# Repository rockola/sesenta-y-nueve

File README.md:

# sesenta-y-nueve

Late 60s Boutique NPN Fuzz Face

* 0.1: initial version, unverified

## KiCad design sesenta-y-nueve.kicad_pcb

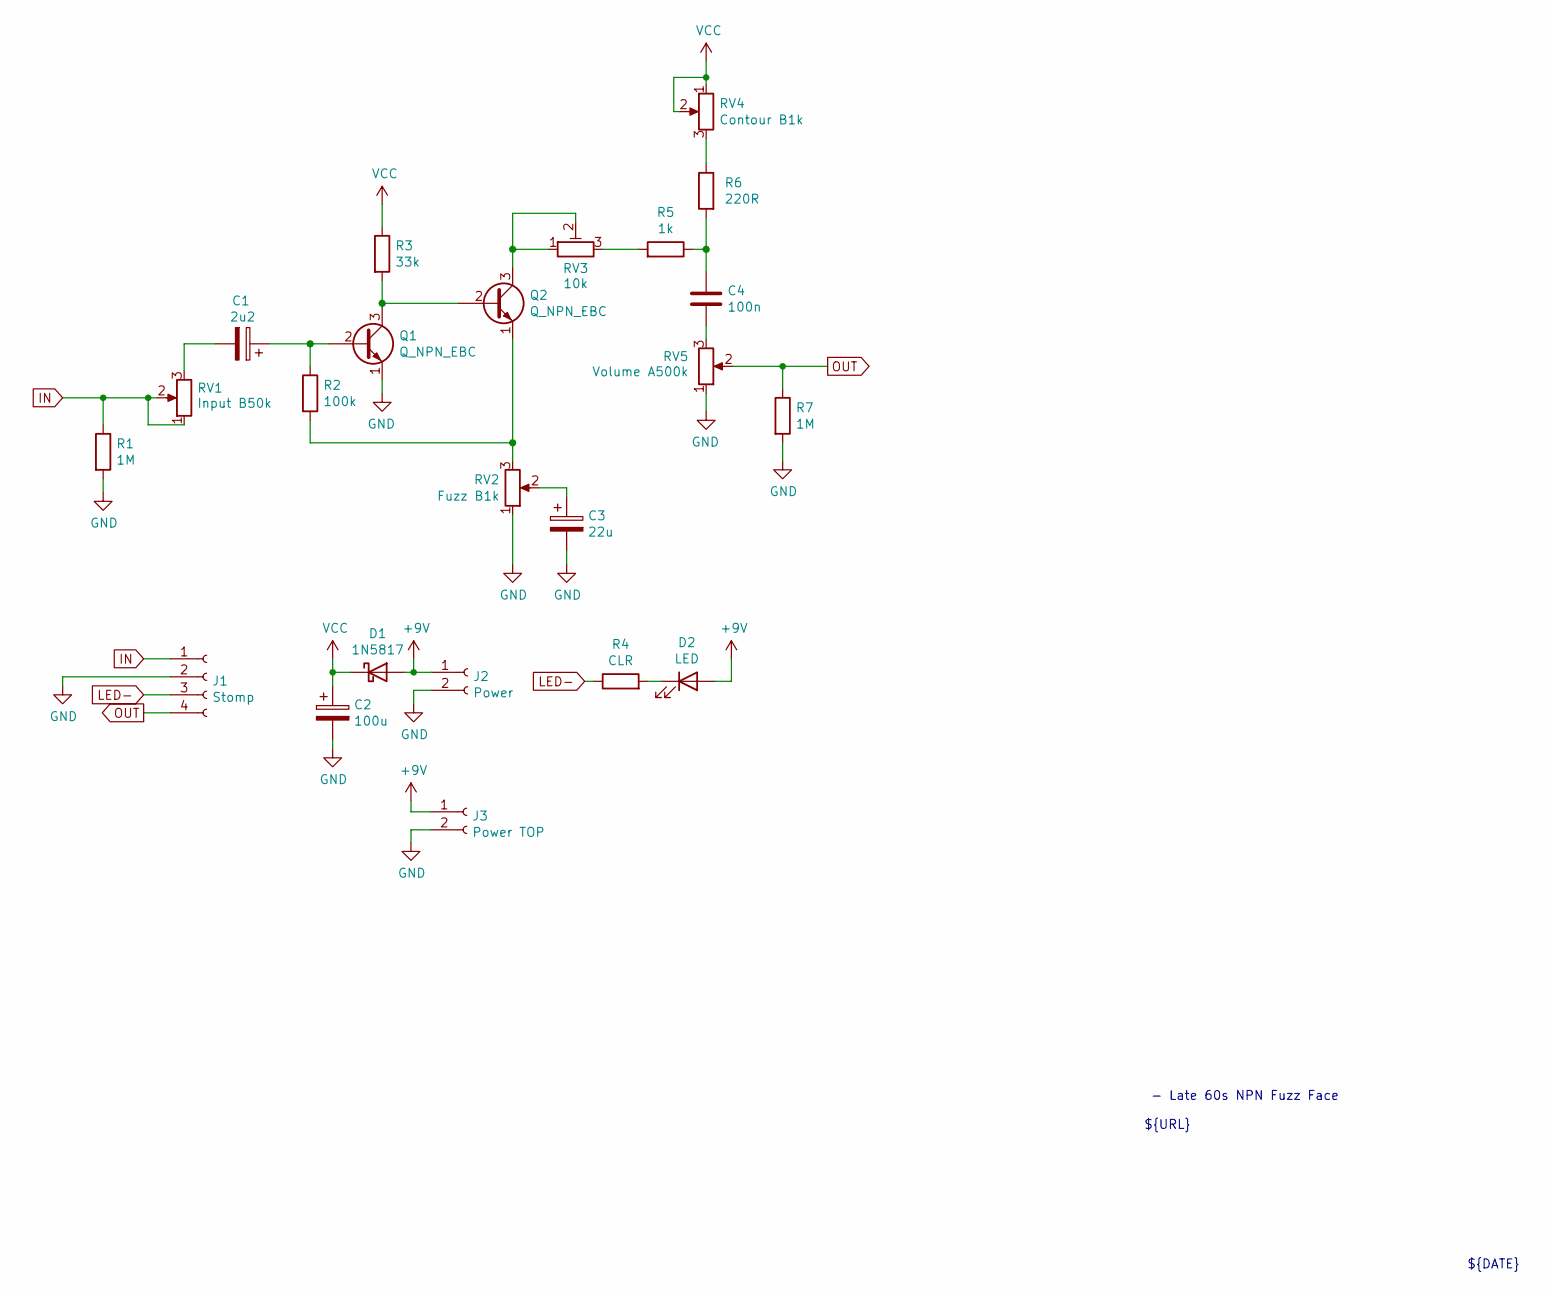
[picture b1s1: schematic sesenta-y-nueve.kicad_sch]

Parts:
C1: 2u2; CP_D5.0_P2.50
C2: 100u; CP_D6.3_P2.50
C3: 22u; CP_D5.0_P2.50
C4: 100n; C_Box_7.2_2.5
D1: 1N5817; D_DO-41_SOD81_P10.16mm_Horizontal
D2: LED; LED.3mm
J1: Stomp; Stomp_4pin
J2: Power; Power_Header_2pin_TOP
J3: Power TOP; Power_Header_2pin_TOP
Q1, Q2: Q_NPN_EBC; TO92_EBC
R1, R7: 1M; R_DIN0207
R2: 100k; R_DIN0207
R3: 33k; R_DIN0207
R4: CLR; R_DIN0207
R5: 1k; R_DIN0207
R6: 220R; R_DIN0207
RV1: Input B50k; 16MM_B.MOUNT
RV2: Fuzz B1k; 16MM_B.MOUNT
RV3: 10k; TRIM1
RV4: Contour B1k; 16MM_B.MOUNT
RV5: Volume A500k; 16MM_B.MOUNT

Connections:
+9V: D1.2 (A), D2.2 (A), J2.1, J3.1
GND: C2.2, C3.2, J1.2, J2.2, J3.2, Q1.1 (E), R1.2, R7.2, RV2.1, RV5.1
IN: J1.1, R1.1, RV1.1, RV1.2
LED-: J1.3, R4.1
unnamed: C1.2, RV1.3
unnamed: C3.1, RV2.2
unnamed: C4.1, R5.1, R6.2
unnamed: C4.2, RV5.3
unnamed: D2.1 (K), R4.2
unnamed: C1.1, Q1.2 (B), R2.1
unnamed: Q1.3 (C), Q2.2 (B), R3.2
unnamed: Q2.1 (E), R2.2, RV2.3
unnamed: Q2.3 (C), RV3.1, RV3.2
unnamed: R5.2, RV3.3
unnamed: R6.1, RV4.3
OUT: J1.4, R7.1, RV5.2
VCC: C2.1, D1.1 (K), R3.1, RV4.1, RV4.2

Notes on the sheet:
${REVISION}
${TITLE} - Late 60s NPN Fuzz Face ${URL}
${TITLE}
${DATE}

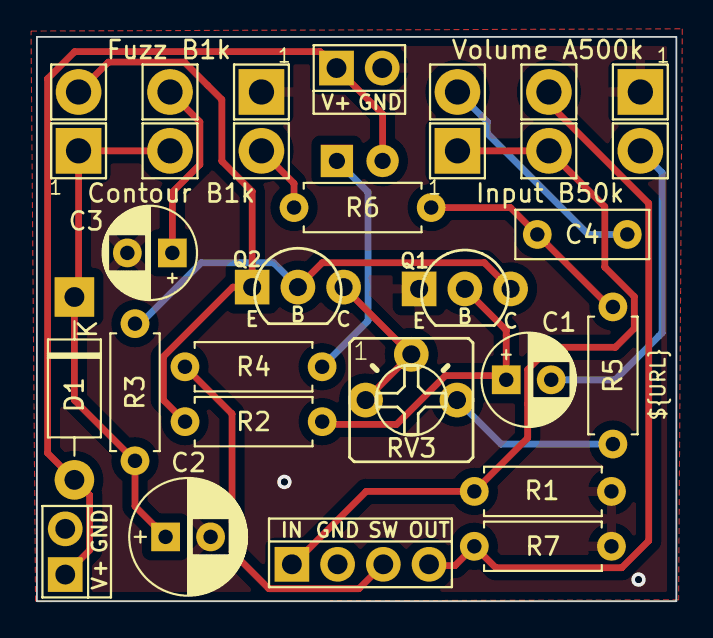
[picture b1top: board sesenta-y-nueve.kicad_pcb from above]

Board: 2 copper layers, 35.5 x 31.3 mm, 23 parts (1 on the bottom side), 17 nets.

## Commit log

2020-12-17 initial v0.1 import
2020-12-17 renamed to be consistent with other projects
2020-12-17 typo
2022-01-11 updated to KiCad 6.0
